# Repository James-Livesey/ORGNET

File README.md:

# ORGNET
A wireless networking peripheral for the Psion Organiser II, in a datapack form factor.

## Getting the code
This repository contains Git submodules that must be cloned to be able to assemble the ORGNET application's code and emulate the Organiser II's firmware. To clone this repository, run:

```bash
git clone --recurse-submodules https://github.com/James-Livesey/ORGNET
```

## Building and running
To build ORGNET's firmware and application, run:

```bash
./build.sh
```

Running this script without any arguments will also upload the firmware and application build to the RP2350 over USB.

To test ORGNET's application in an emulator, run:

```bash
pushd app; ./build.sh --test; popd
```

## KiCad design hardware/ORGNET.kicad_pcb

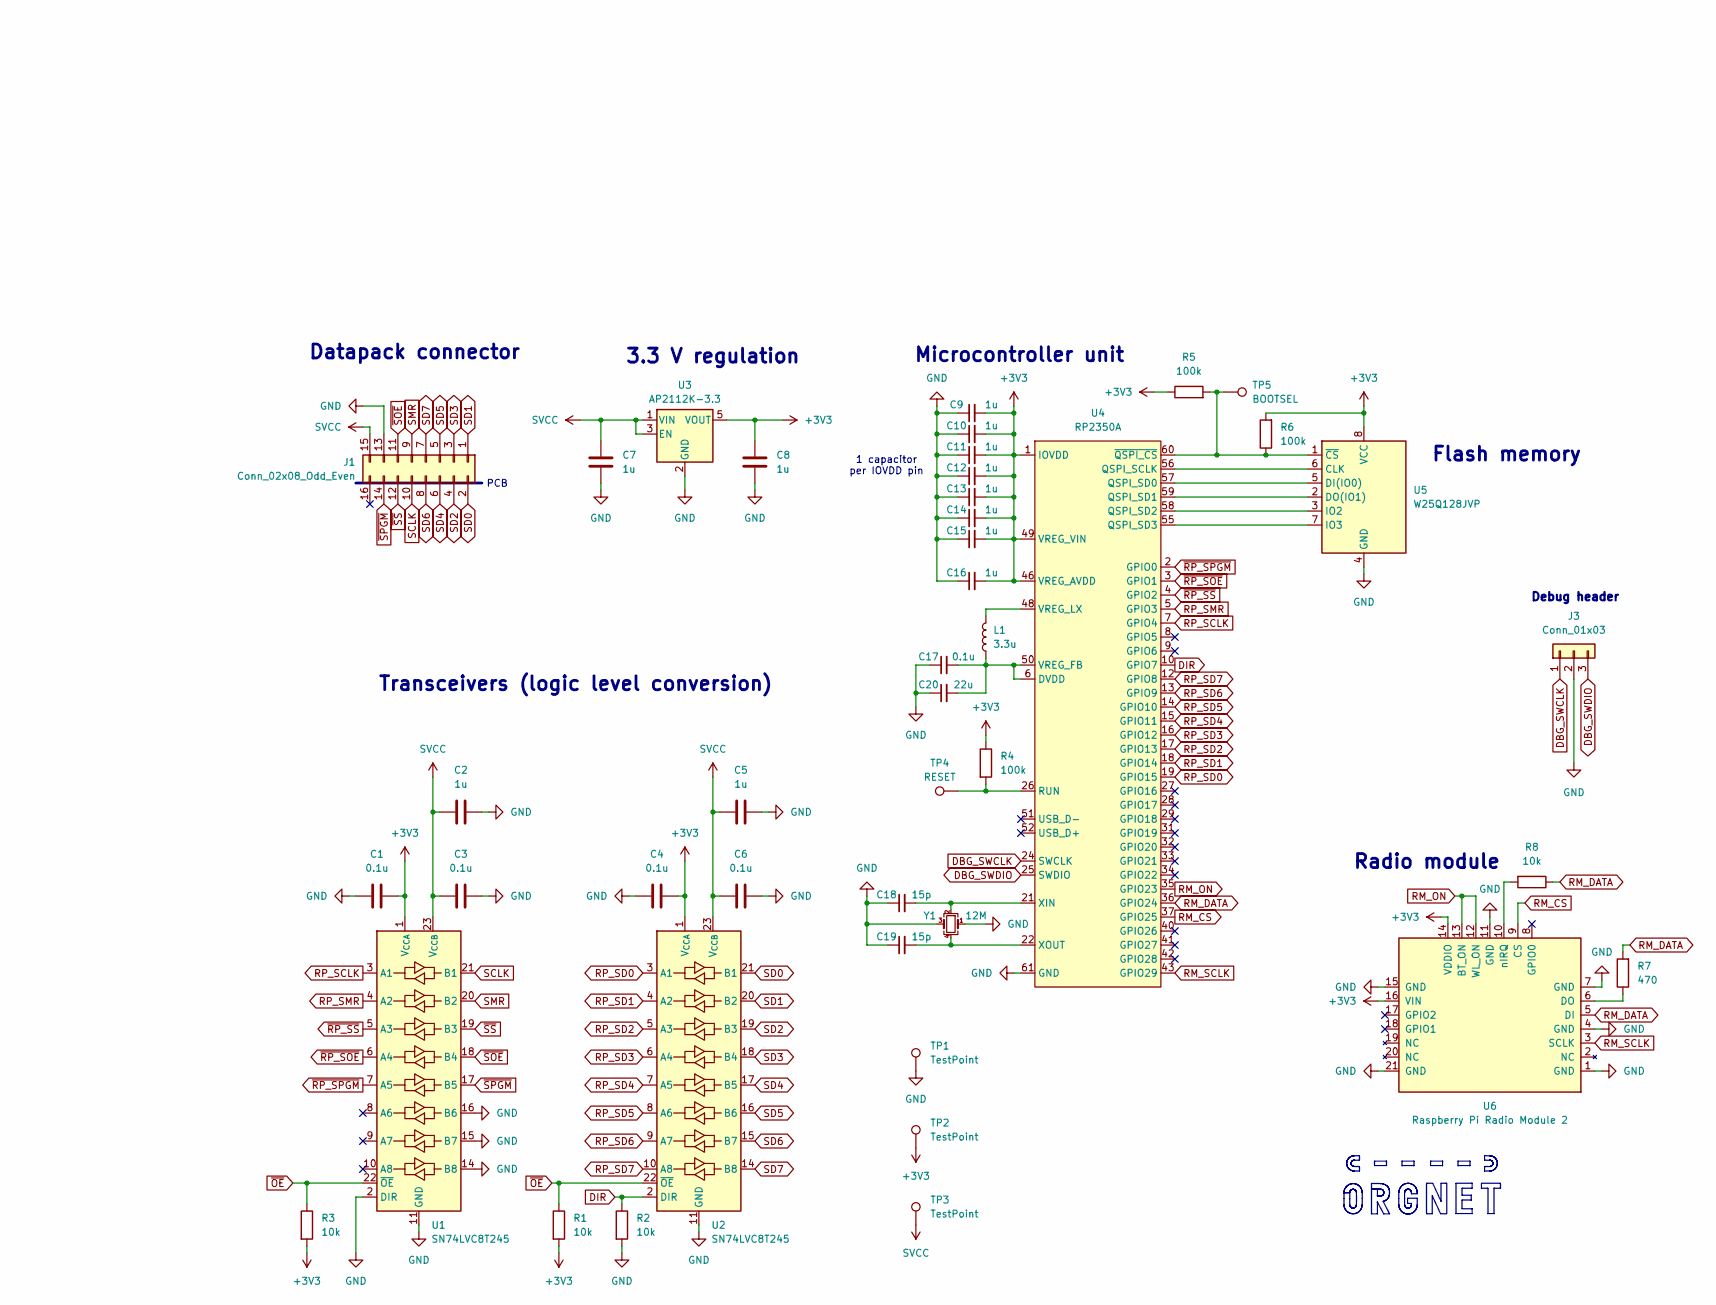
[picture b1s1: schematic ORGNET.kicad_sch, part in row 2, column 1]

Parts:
C1, C3, C4, C6, C17: 0.1u; C_0402_1005Metric_Pad0.74x0.62mm_HandSolder
C2, C5, C7, C8, C9, C10, C11, C12, C13, C14, C15, C16: 1u; C_0402_1005Metric_Pad0.74x0.62mm_HandSolder
C18, C19: 15p; C_0402_1005Metric_Pad0.74x0.62mm_HandSolder
C20: 22u; C_0402_1005Metric_Pad0.74x0.62mm_HandSolder
J1: Conn_02x08_Odd_Even; PinSocket_2x08_P2.54mm_Horizontal
J3: Conn_01x03; JST_SH_BM03B-SRSS-TB_1x03-1MP_P1.00mm_Vertical
L1: 3.3u; L_1210_3225Metric_Pad1.42x2.65mm_HandSolder
R1, R2, R3, R8: 10k; R_0402_1005Metric_Pad0.72x0.64mm_HandSolder
R4, R5, R6: 100k; R_0402_1005Metric_Pad0.72x0.64mm_HandSolder
R7: 470; R_0402_1005Metric_Pad0.72x0.64mm_HandSolder
TP1, TP2, TP3: TestPoint; TestPoint_Pad_D2.0mm
TP4: RESET; TestPoint_Pad_D2.0mm
TP5: BOOTSEL; TestPoint_Pad_D2.0mm
U1, U2: SN74LVC8T245; TSSOP-24_4.4x7.8mm_P0.65mm
U3: AP2112K-3.3; SOT-23-5
U4: RP2350A; QFN-60-1EP_7x7mm_P0.4mm_EP3.4x3.4mm
U5: W25Q128JVP; WSON-8-1EP_6x5mm_P1.27mm_EP3.4x4.3mm
U6: Raspberry Pi Radio Module 2; rpi_rmc20452t
Y1: 12M; Crystal_SMD_Abracon_ABM8G-4Pin_3.2x2.5mm

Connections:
+3V3: C1.1, C4.1, C8.1, C9.2, C10.2, C11.2, C12.2, C13.2, C14.2, C15.2, C16.2, R1.2, R3.2, R4.1, R5.1, R6.2, TP2.1, U1.1 (V_{CCA}), U2.1 (V_{CCA}), U3.5 (VOUT), U4.1 (IOVDD), U4.11 (IOVDD), U4.20 (IOVDD), U4.30 (IOVDD), U4.38 (IOVDD), U4.44 (IOVDD), U4.45 (IOVDD), U4.46 (VREG_AVDD), U4.49 (VREG_VIN), U4.53 (IOVDD), U4.54 (IOVDD), U5.8 (VCC), U6.14 (VDDIO), U6.16 (VIN)
DBG_SWCLK: J3.1, U4.24 (SWCLK)
DBG_SWDIO: J3.3, U4.25 (SWDIO)
DIR: R2.1, U2.2 (DIR), U4.10 (GPIO7)
GND: C1.2, C2.1, C3.1, C4.2, C5.1, C6.1, C7.2, C8.2, C9.1, C10.1, C11.1, C12.1, C13.1, C14.1, C15.1, C16.1, C17.1, C18.1, C19.1, C20.1, J1.13, J3.2, R2.2, TP1.1, U1.2 (DIR), U1.11 (GND), U1.12 (GND), U1.13 (GND), U1.14 (B8), U1.15 (B7), U1.16 (B6), U2.11 (GND), U2.12 (GND), U2.13 (GND), U3.2 (GND), U4.47 (GND), U4.61 (GND), U5.4 (GND), U6.1 (GND), U6.4 (GND), U6.7 (GND), U6.11 (GND), U6.15 (GND), U6.21 (GND), Y1.1, Y1.3
unnamed: U4.56 (QSPI_SCLK), U5.6 (CLK)
unnamed: U4.57 (QSPI_SD0), U5.5 (DI(IO0))
unnamed: U4.59 (QSPI_SD1), U5.2 (DO(IO1))
unnamed: U4.58 (QSPI_SD2), U5.3 (IO2)
unnamed: U4.55 (QSPI_SD3), U5.7 (IO3)
unnamed: R4.2, TP4.1, U4.26 (RUN)
unnamed: C17.2, C20.2, L1.1, U4.6 (DVDD), U4.23 (DVDD), U4.39 (DVDD), U4.50 (VREG_FB)
unnamed: L1.2, U4.48 (VREG_LX)
unnamed: C18.2, U4.21 (XIN), Y1.2
unnamed: C19.2, U4.22 (XOUT), Y1.4
unnamed: R5.2, R6.1, TP5.1, U4.60 (~QSPI_CS), U5.1 (~CS)
unnamed: R7.1, U6.6 (DO)
unnamed: R8.2, U6.10 (nIRQ)
RM_CS: U4.37 (GPIO25), U6.9 (CS)
RM_DATA: R7.2, R8.1, U4.36 (GPIO24), U6.5 (DI)
RM_ON: U4.35 (GPIO23), U6.12 (WL_ON), U6.13 (BT_ON)
RM_SCLK: U4.43 (GPIO29), U6.3 (SCLK)
RP_SCLK: U1.3 (A1), U4.7 (GPIO4)
RP_SD0: U2.3 (A1), U4.19 (GPIO15)
RP_SD1: U2.4 (A2), U4.18 (GPIO14)
RP_SD2: U2.5 (A3), U4.17 (GPIO13)
RP_SD3: U2.6 (A4), U4.16 (GPIO12)
RP_SD4: U2.7 (A5), U4.15 (GPIO11)
RP_SD5: U2.8 (A6), U4.14 (GPIO10)
RP_SD6: U2.9 (A7), U4.13 (GPIO9)
RP_SD7: U2.10 (A8), U4.12 (GPIO8)
RP_SMR: U1.4 (A2), U4.5 (GPIO3)
SCLK: J1.10, U1.21 (B1)
SD0: J1.2, U2.21 (B1)
SD1: J1.1, U2.20 (B2)
SD2: J1.4, U2.19 (B3)
SD3: J1.3, U2.18 (B4)
SD4: J1.6, U2.17 (B5)
SD5: J1.5, U2.16 (B6)
SD6: J1.8, U2.15 (B7)
SD7: J1.7, U2.14 (B8)
SMR: J1.9, U1.20 (B2)
SVCC: C2.2, C3.2, C5.2, C6.2, C7.1, J1.15, TP3.1, U1.23 (V_{CCB}), U1.24 (V_{CCB}), U2.23 (V_{CCB}), U2.24 (V_{CCB}), U3.1 (VIN), U3.3 (EN)
~OE: R1.1, R3.1, U1.22 (~OE), U2.22 (~OE)
~RP_SOE: U1.6 (A4), U4.3 (GPIO1)
~RP_SPGM: U1.7 (A5), U4.2 (GPIO0)
~RP_SS: U1.5 (A3), U4.4 (GPIO2)
~SOE: J1.11, U1.18 (B4)
~SPGM: J1.14, U1.17 (B5)
~SS: J1.12, U1.19 (B3)

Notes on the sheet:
Flash memory
Microcontroller unit
PCB
Debug header
3.3 V regulation
1 capacitor per IOVDD pin
Datapack connector
Transceivers (logic level conversion)
Radio module

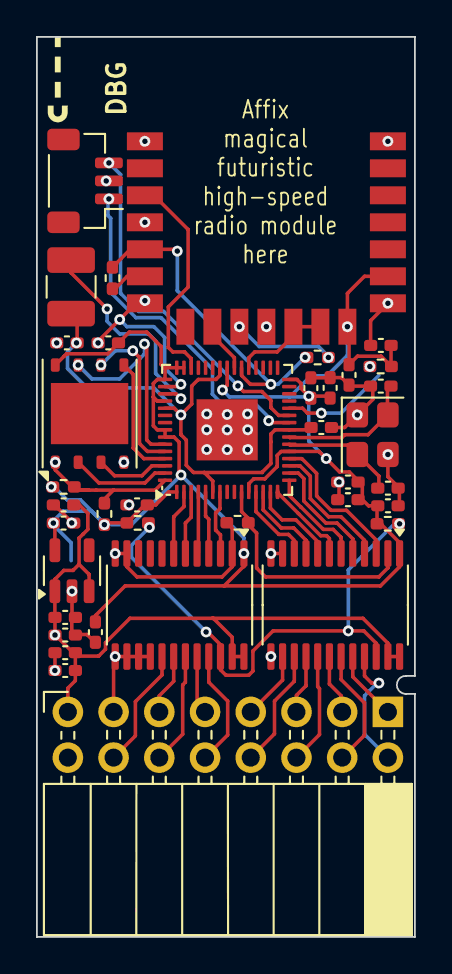
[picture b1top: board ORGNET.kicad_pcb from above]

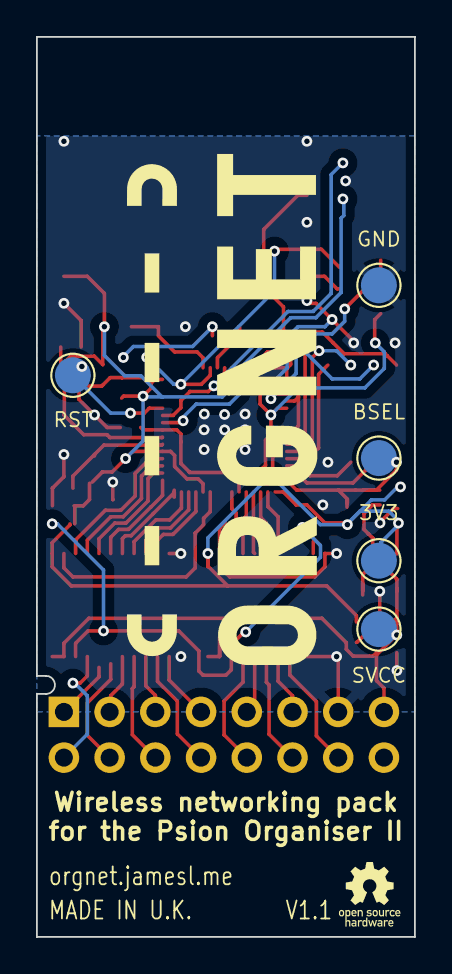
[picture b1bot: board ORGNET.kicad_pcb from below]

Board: 2 copper layers, 21.0 x 50.0 mm, 43 parts (5 on the bottom side), 50 nets.

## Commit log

2025-07-17 Add readme
2025-07-17 Add licence
2025-07-17 Create basic schematic for hardware
2025-07-18 Add note about repo having submodules to readme
2025-07-18 Add expansion and debug headers
2025-07-19 Begin laying out footprints on PCB
2025-07-21 Start routing PCB
2025-07-21 Finish off PCB routing
2025-07-22 Fix order of pins on connector
2025-07-22 Add logo and branding to PCB
2025-07-22 Add branding to schematics
2025-07-22 Fix logo colour on schematic
2025-07-23 Make a few minor changes to PCB layout and silkscreen
2025-07-23 Implement a few more minor PCB tweaks
2025-07-23 Remove unused ground plane vias
2025-07-26 Add Gerber files
2025-07-26 Add notch and use 0406 resistors/capacitors
2025-07-29 Make minor fixes to PCB layout
2025-09-03 Update schematic to fix MCU overheating
2025-09-17 Implement minimal datapack demo
2025-09-17 Add basic assembly code to include in firmware
2025-09-17 Add code to show ORGNET logo in install vector
2025-09-17 Fix very minor inconsistency with docstrings
2025-09-18 Fix indentation in assembly files
2025-09-18 Fix more indentation
2025-09-18 Prevent pack auto switch-off when ORGNET is in use
2025-09-19 Fix power routing to address short circuiting issue
2025-09-19 Change pack ID to be RAM-based
2025-09-20 Refactor app code to move NETCFG code to new file
2025-09-20 Add main menu and about area to NETCFG application
2025-09-21 Implement comms buffer with bidirectional communications
2025-09-21 Get command handling working on RP2350 side
2025-09-22 Add basics of Wi-Fi status screen
2025-09-23 Load basic test data into Wi-Fi status screen
2025-09-24 Remove temprary test command
2025-09-25 Add error code to error message translation
2025-09-26 Add details about building and running to readme
2025-09-27 Add note about testing in emulator
2025-10-05 Add minor clarification to readme about uploading firmware
2025-10-06 Add description about required components to readme
2025-10-07 Make minor change to wording in readme
2025-10-08 Make minor improvement to clarity in readme
2025-10-09 Make minor modification to comments in netcfg code
2025-10-13 Make minor clarification to running build script in readme
2025-10-14 Make minor adjustment to description of a subroutine
2025-10-15 Clarify error handling subroutine's description
2025-10-16 Add more detail to `netcfg_main` description
2025-10-30 Don't use error macro as it is more confusing than not using it
2025-10-31 Create mock version of comms manager to test in emulator
2025-10-31 Implement command matching to generate mock responses
2025-11-01 Create architecture diagram for datapack and RAM layout
2025-11-01 Make some core routines vectors so that they can be called from another allocator cell
2025-11-02 Add start of app loader code
2025-11-02 Get app loading working for `NETCFG` app
2025-11-02 Add some comments to clarify code in app vector
2025-11-02 Fix description of core routine vectors code
2025-11-03 Add polling for Wi-Fi connection status screen
2025-11-04 Display connection strength character on Wi-Fi status screen
2025-11-05 Add start of Wi-Fi options menu
2025-11-06 Fix issue with non-blocking keypress testing, and other issues
2025-11-07 Make minor grammar fix in readme
2025-11-08 Fix scroll offset rendering in line renderer
2025-11-09 Clarify comment in line rendering code
2025-11-10 Implement line scrolling behaviour
2025-11-11 Implement cached line rendering when scrolling horizontally
2025-11-12 Draw cursor when showing lines and use cached line
2025-11-13 Improve some comments to be less redundant
2025-12-02 Make minor addition to readme description
2025-12-09 Remove hotspot-related code as hotspot checks will be done by caller
2025-12-09 Implement scroll Y limit in line renderer
2025-12-10 Add option to prevent horizontal scrolling in line renderer
2025-12-11 Return current scroll position values from `line_show` subroutine
2025-12-12 Add loop to netcfg code to only exit connection menu when correct key is pressed
2025-12-13 Add mock command and response for Wi-Fi SSID list
2025-12-13 Implement netcfg connection list based on mock comms
2025-12-15 Add option to netcfg newcon menu to add unlisted networks
2025-12-16 Add input to enter SSID of unlisted networks
2025-12-17 Implement basic Wi-Fi listing commands on Pi Pico side
2025-12-18 Fix C++20 language feature config in VSCode
2025-12-18 Add Wi-Fi scanning on Pi Pico side (WIP)
2025-12-19 Make minor grammar fix to readme
2025-12-20 Make minor clarification to comment
2025-12-21 Change clock speed and init Wi-Fi when needed
2026-05-28 Rename 'app' to 'service' as main apps will be written in OPL
2026-05-28 Fix app code references
2026-05-28 Modify toolchain to translate and include OPL code as part of datapack
2026-05-28 Allow full compilation by modifying firmware
2026-05-28 Uncomment firmware uploader command
2026-05-28 Fix comms error and try making Wi-Fi more reliable
2026-05-29 Fix pack type when running in emulator
2026-05-29 Start rewriting NETCFG app in OPL
2026-05-30 Mock disconnection when DISCON or FORGET selected
